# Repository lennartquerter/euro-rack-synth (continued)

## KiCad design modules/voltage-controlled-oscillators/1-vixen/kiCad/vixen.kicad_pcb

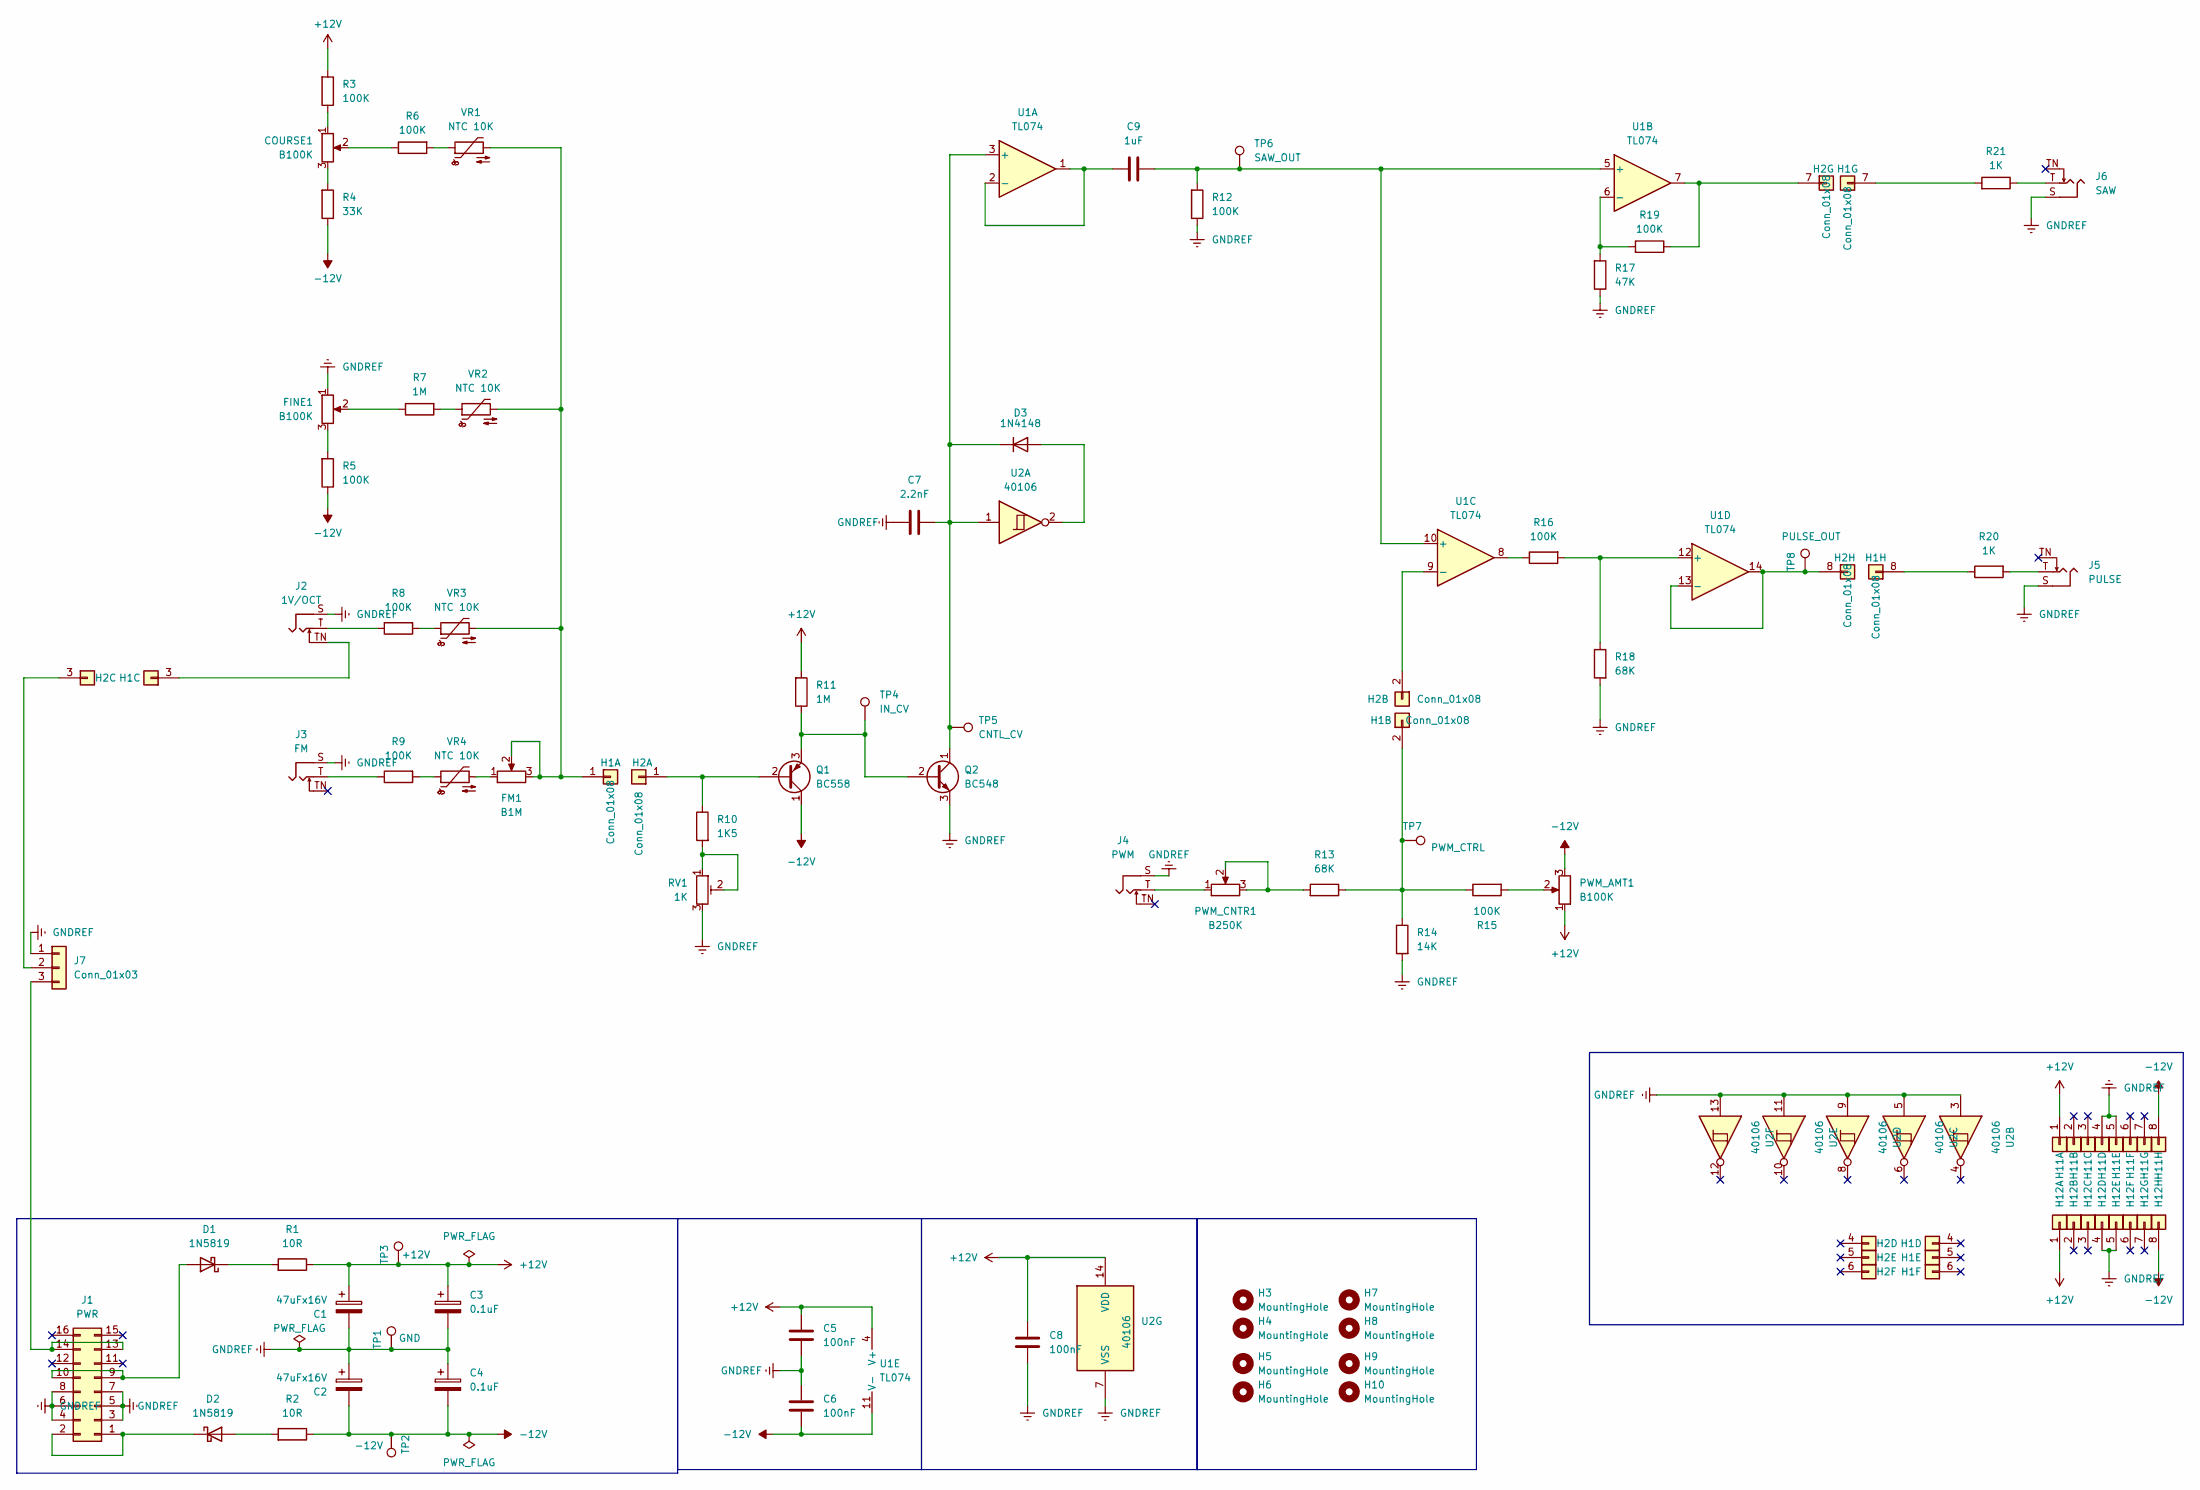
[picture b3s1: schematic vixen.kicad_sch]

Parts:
C1, C2: 47uFx16V; CP_Radial_D5.0mm_P2.00mm
C3, C4: 0.1uF; CP_Radial_D4.0mm_P2.00mm
C5, C6, C8: 100nF; C_RECT_WIMA_0.1uF
C7: 2.2nF; C_RECT_WIMA_0.1uF
C9: 1uF; C_RECT_MKT_1uF
COURSE1: B100K; Potentiometer_TT_P0915N
D1, D2: 1N5819; D_DO-41_SOD81_P10.16mm_Horizontal
D3: 1N4148; D_DO-35_SOD27_P7.62mm_Horizontal
FINE1: B100K; Potentiometer_TT_P0915N
FM1: B1M; Potentiometer_TT_P0915N
H1, H12: Conn_01x08; PinHeader_1x08_P2.54mm_Vertical
H2, H11: Conn_01x08; PinSocket_1x08_P2.54mm_Vertical
H3, H4, H5, H6, H7, H8, H9, H10: MountingHole; MountingHole_3.5mm
J1: PWR; IDC-Header_2x08_P2.54mm_Vertical
J2: 1V/OCT; Jack_3.5mm_QingPu_WQP-PJ398SM_Vertical_CircularHoles
J3: FM; Jack_3.5mm_QingPu_WQP-PJ398SM_Vertical_CircularHoles
J4: PWM; Jack_3.5mm_QingPu_WQP-PJ398SM_Vertical_CircularHoles
J5: PULSE; Jack_3.5mm_QingPu_WQP-PJ398SM_Vertical_CircularHoles
J6: SAW; Jack_3.5mm_QingPu_WQP-PJ398SM_Vertical_CircularHoles
J7: Conn_01x03; PinHeader_1x03_P2.54mm_Vertical
PWM_AMT1: B100K; Potentiometer_TT_P0915N
PWM_CNTR1: B250K; Potentiometer_Alpha_RD901F-40-00D_Single_Vertical_CircularH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
Q1: BC558; TO-92_HandSolder
Q2: BC548; TO-92_HandSolder
R1, R2: 10R; R_Default (DIN0207)
R3, R5, R6, R8, R9, R12, R15, R16, R19: 100K; R_Default (DIN0207)
R4: 33K; R_Default (DIN0207)
R7, R11: 1M; R_Default (DIN0207)
R10: 1K5; R_Default (DIN0207)
R13, R18: 68K; R_Default (DIN0207)
R14: 14K; R_Default (DIN0207)
R17: 47K; R_Default (DIN0207)
R20, R21: 1K; R_Default (DIN0207)
RV1: 1K; Potentiometer_Bourns_3296W_Vertical
TP1: GND; Pin_D1.0mm_L10.0mm
TP2: -12V; Pin_D1.0mm_L10.0mm
TP3: +12V; Pin_D1.0mm_L10.0mm
TP4: IN_CV; Pin_D1.0mm_L10.0mm
TP5: CNTL_CV; Pin_D1.0mm_L10.0mm
TP6: SAW_OUT; Pin_D1.0mm_L10.0mm
TP7: PWM_CTRL; Pin_D1.0mm_L10.0mm
TP8: PULSE_OUT; Pin_D1.0mm_L10.0mm
U1: TL074; DIP-14_W7.62mm_Socket_LongPads
U2: 40106; DIP-14_W7.62mm_Socket_LongPads
VR1, VR2, VR3, VR4: NTC 10K; R_Axial_DIN0207_L6.3mm_D2.5mm_P5.08mm_Vertical

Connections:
+12V: C1.1, C3.1, C5.1, C8.1, H11.1 (Pin_3), H12.1, PWM_AMT1.1, R1.2, R3.1, R11.1, TP3.1, U1.4 (V+), U2.14 (VDD)
-12V: C2.2, C4.2, C6.2, H11.8, H12.8, PWM_AMT1.3, Q1.1 (C), R2.2, R4.2, R5.2, TP2.1, U1.11 (V-)
GNDREF: C1.2, C2.1, C3.2, C4.1, C5.2, C6.1, C7.2, C8.2, FINE1.1, H11.4, H11.5, H12.4, H12.5, J1.3 (GND), J1.4 (GND), J1.5 (GND), J1.6 (GND), J1.7 (GND), J1.8 (GND), J2.S, J3.S, J4.S, J5.S, J6.S, J7.1, Q2.3 (E), R12.2, R14.1, R17.2, R18.1, RV1.3, TP1.1, U2.3, U2.5, U2.7 (VSS), U2.9, U2.11, U2.13
unnamed: COURSE1.1, R3.2
unnamed: COURSE1.2, R6.2
unnamed: COURSE1.3, R4.1
unnamed: D1.2 (A), J1.9 (+12V), J1.10 (+12V)
unnamed: D1.1 (K), R1.1
unnamed: D2.2 (A), R2.1
unnamed: D2.1 (K), J1.1 (-12V), J1.2 (-12V)
unnamed: D3.2 (A), U2.2
unnamed: C7.1, D3.1 (K), Q2.1 (C), TP5.1, U1.3 (+), U2.1
unnamed: FINE1.2, R7.2
unnamed: FINE1.3, R5.1
unnamed: FM1.1, VR4.2
unnamed: FM1.2, FM1.3, H1.1, VR1.2, VR2.2, VR3.2
unnamed: H1.2, R13.2, R14.2, R15.2, TP7.1
unnamed: H1.3, J2.TN
unnamed: H1.7, R21.1
unnamed: H1.8, R20.2
unnamed: H2.1 (Pin_3), Q1.2 (B), R10.2
unnamed: H2.2, U1.9 (-)
unnamed: H2.3, J7.2
unnamed: H2.7, R19.2, U1.7
unnamed: H2.8, TP8.1, U1.13 (-), U1.14
unnamed: J2.T, R8.2
unnamed: J3.T, R9.2
unnamed: J4.T, PWM_CNTR1.1
unnamed: J5.T, R20.1
unnamed: J6.T, R21.2
unnamed: J1.13 (CV), J1.14 (CV), J7.3
unnamed: PWM_AMT1.2, R15.1
unnamed: PWM_CNTR1.2, PWM_CNTR1.3, R13.1
unnamed: Q1.3 (E), Q2.2 (B), R11.2, TP4.1
unnamed: R6.1, VR1.1
unnamed: R7.1, VR2.1
unnamed: R8.1, VR3.1
unnamed: R9.1, VR4.1
unnamed: R10.1, RV1.1, RV1.2
unnamed: R16.2, U1.8
unnamed: C9.1, U1.1, U1.2 (-)
unnamed: C9.2, R12.1, TP6.1, U1.5 (+), U1.10 (+)
unnamed: R17.1, R19.1, U1.6 (-)
unnamed: R16.1, R18.2, U1.12 (+)

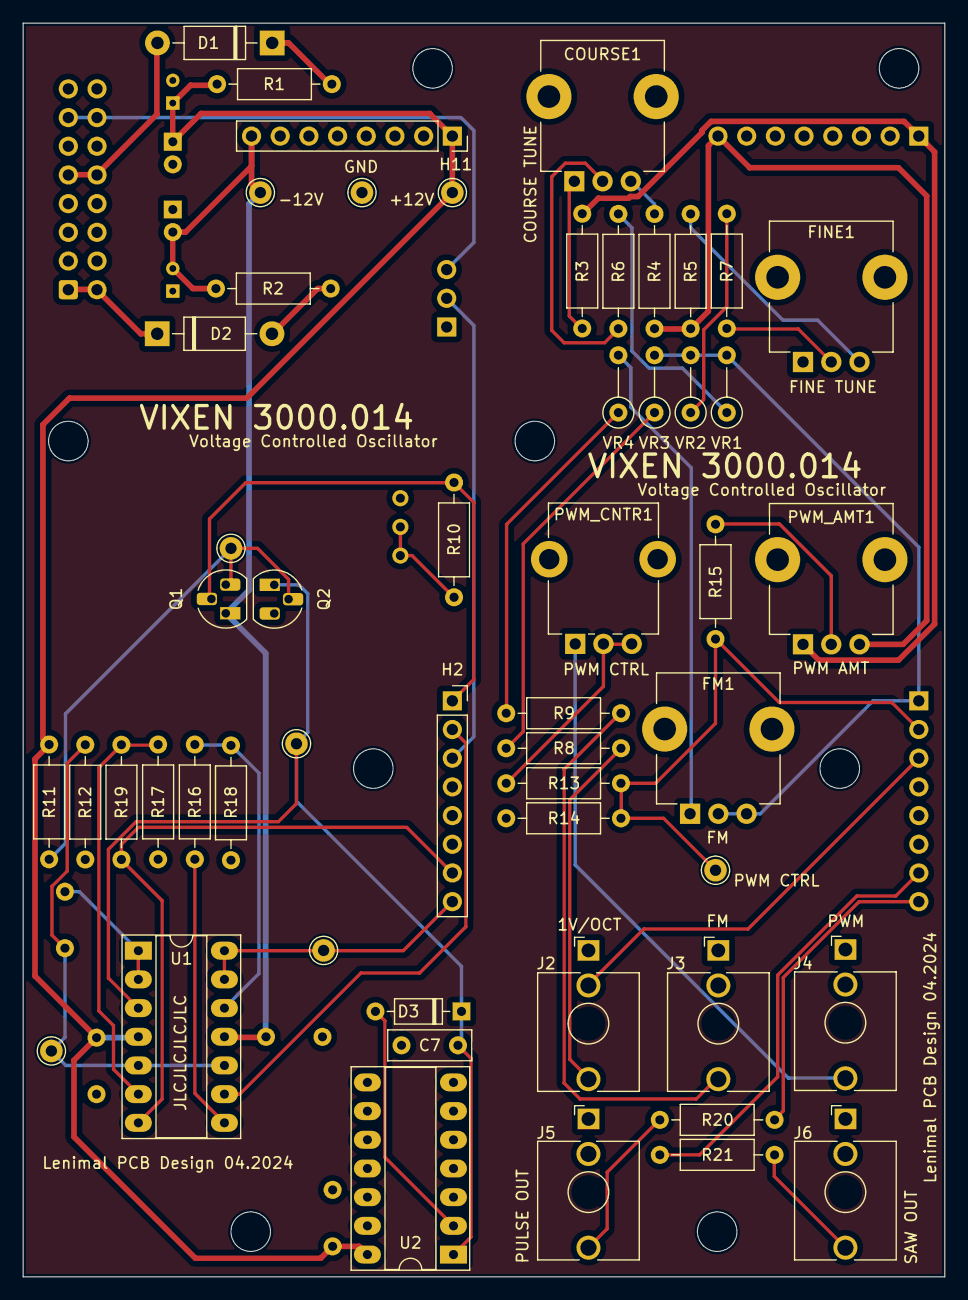
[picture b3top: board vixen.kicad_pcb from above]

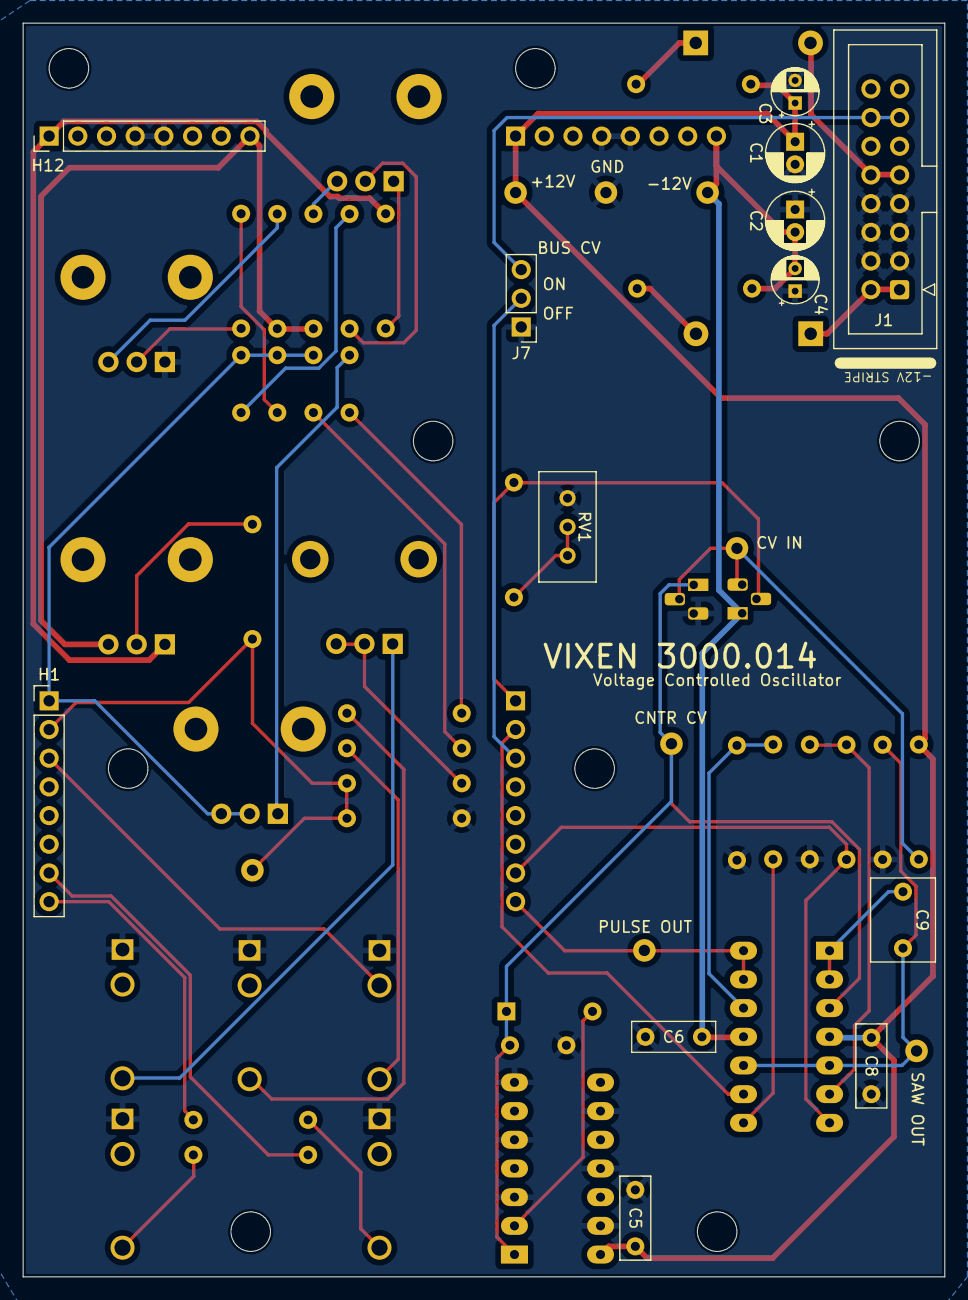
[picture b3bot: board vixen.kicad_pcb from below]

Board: 2 copper layers, 81.6 x 111.0 mm, 74 parts (13 on the bottom side), 44 nets.

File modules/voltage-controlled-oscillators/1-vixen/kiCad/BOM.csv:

"Reference","Value","Datasheet","Footprint","Qty","DNP"
"C1,C2","47uFx16V","~","Capacitor_THT:CP_Radial_D5.0mm_P2.00mm","2",""
"C3,C4,C5,C6,C8","0.1uF","~","Capacitor_THT:CP_Radial_D4.0mm_P2.00mm","5",""
"C7","2.2nF","~","Synth:C_RECT_WIMA_0.1uF","1",""
"C9","1 uF","~","Synth:C_RECT_MKT_1uF","1",""
"COURSE1,FINE1,PWM_AMT1","B100K","~","Synth:Potentiometer_TT_P0915N","3",""
"D1,D2","1N5819","http://www.vishay.com/docs/88525/1n5817.pdf","Synth:D_DO-41_SOD81_P10.16mm_Horizontal","2",""
"D3","1N4148","https://assets.nexperia.com/documents/data-sheet/1N4148_1N4448.pdf","Synth:D_DO-35_SOD27_P7.62mm_Horizontal","1",""
"FM1","B1M","~","Synth:Potentiometer_TT_P0915N","1",""
"H1","TOP_SGN","~","Synth:PinHeader_1x08_P2.54mm_Vertical","1",""
"H2","BTN_SGN","~","Synth:PinSocket_1x08_P2.54mm_Vertical","1",""
"H3,H4,H5,H6,H7,H8,H9,H10","MountingHole","~","MountingHole:MountingHole_3.5mm","8",""
"H11","BTM_PWR","~","Synth:PinSocket_1x08_P2.54mm_Vertical","1",""
"H12","TOP_PWR","~","Synth:PinHeader_1x08_P2.54mm_Vertical","1",""
"J1","PWR","~","Synth:IDC-Header_2x08_P2.54mm_Vertical","1",""
"J2","1V/OCT","~","Synth:Jack_3.5mm_QingPu_WQP-PJ398SM_Vertical_CircularHoles","1",""
"J3","FM","~","Synth:Jack_3.5mm_QingPu_WQP-PJ398SM_Vertical_CircularHoles","1",""
"J4","PWM","~","Synth:Jack_3.5mm_QingPu_WQP-PJ398SM_Vertical_CircularHoles","1",""
"J5","PULSE","~","Synth:Jack_3.5mm_QingPu_WQP-PJ398SM_Vertical_CircularHoles","1",""
"J6","SAW","~","Synth:Jack_3.5mm_QingPu_WQP-PJ398SM_Vertical_CircularHoles","1",""
"J7","Conn_01x03","~","Connector_PinHeader_2.54mm:PinHeader_1x03_P2.54mm_Vertical","1",""
"PWM_CNTR1","B250K","~","Synth:Potentiometer_Alpha_RD901F-40-00D_Single_Vertical_CircularHoles","1",""
"Q1","BC558","https://www.onsemi.com/pub/Collateral/BC556BTA-D.pdf","Package_TO_SOT_THT:TO-92_Inline","1",""
"Q2","BC548","https://www.onsemi.com/pub/Collateral/BC550-D.pdf","Package_TO_SOT_THT:TO-92_Inline","1",""
"R1,R2","10","~","Synth:R_Default (DIN0207)","2",""
"R3,R5,R6,R8,R9,R12,R15,R16,R19","100K","~","Synth:R_Default (DIN0207)","9",""
"R4","33K","~","Synth:R_Default (DIN0207)","1",""
"R7,R11","1M","~","Synth:R_Default (DIN0207)","2",""
"R10","1.5K","~","Synth:R_Default (DIN0207)","1",""
"R13,R18","68K","~","Synth:R_Default (DIN0207)","2",""
"R14","14K","~","Synth:R_Default (DIN0207)","1",""
"R17","47K","~","Synth:R_Default (DIN0207)","1",""
"R20,R21,RV1","1K","~","-- mixed values --","3",""
"TP1","GND","~","Connector_Pin:Pin_D1.0mm_L10.0mm","1",""
"TP2","-12V","~","Connector_Pin:Pin_D1.0mm_L10.0mm","1",""
"TP3","+12V","~","Connector_Pin:Pin_D1.0mm_L10.0mm","1",""
"TP4","IN_CV","~","Connector_Pin:Pin_D1.0mm_L10.0mm","1",""
"TP5","CNTL_CV","~","Connector_Pin:Pin_D1.0mm_L10.0mm","1",""
"TP6","SAW_OUT","~","Connector_Pin:Pin_D1.0mm_L10.0mm","1",""
"TP7","PWM_CTRL","~","Connector_Pin:Pin_D1.0mm_L10.0mm","1",""
"TP8","PULSE_OUT","~","Connector_Pin:Pin_D1.0mm_L10.0mm","1",""
"U1","TL074","http://www.ti.com/lit/ds/symlink/tl071.pdf","Package_DIP:DIP-14_W7.62mm_Socket_LongPads","1",""
"U2","40106","https://assets.nexperia.com/documents/data-sheet/HEF40106B.pdf","Package_DIP:DIP-14_W7.62mm_Socket_LongPads","1",""
"VR1,VR2,VR3,VR4","NTC 10K","~","Resistor_THT:R_Axial_DIN0207_L6.3mm_D2.5mm_P5.08mm_Vertical","4",""

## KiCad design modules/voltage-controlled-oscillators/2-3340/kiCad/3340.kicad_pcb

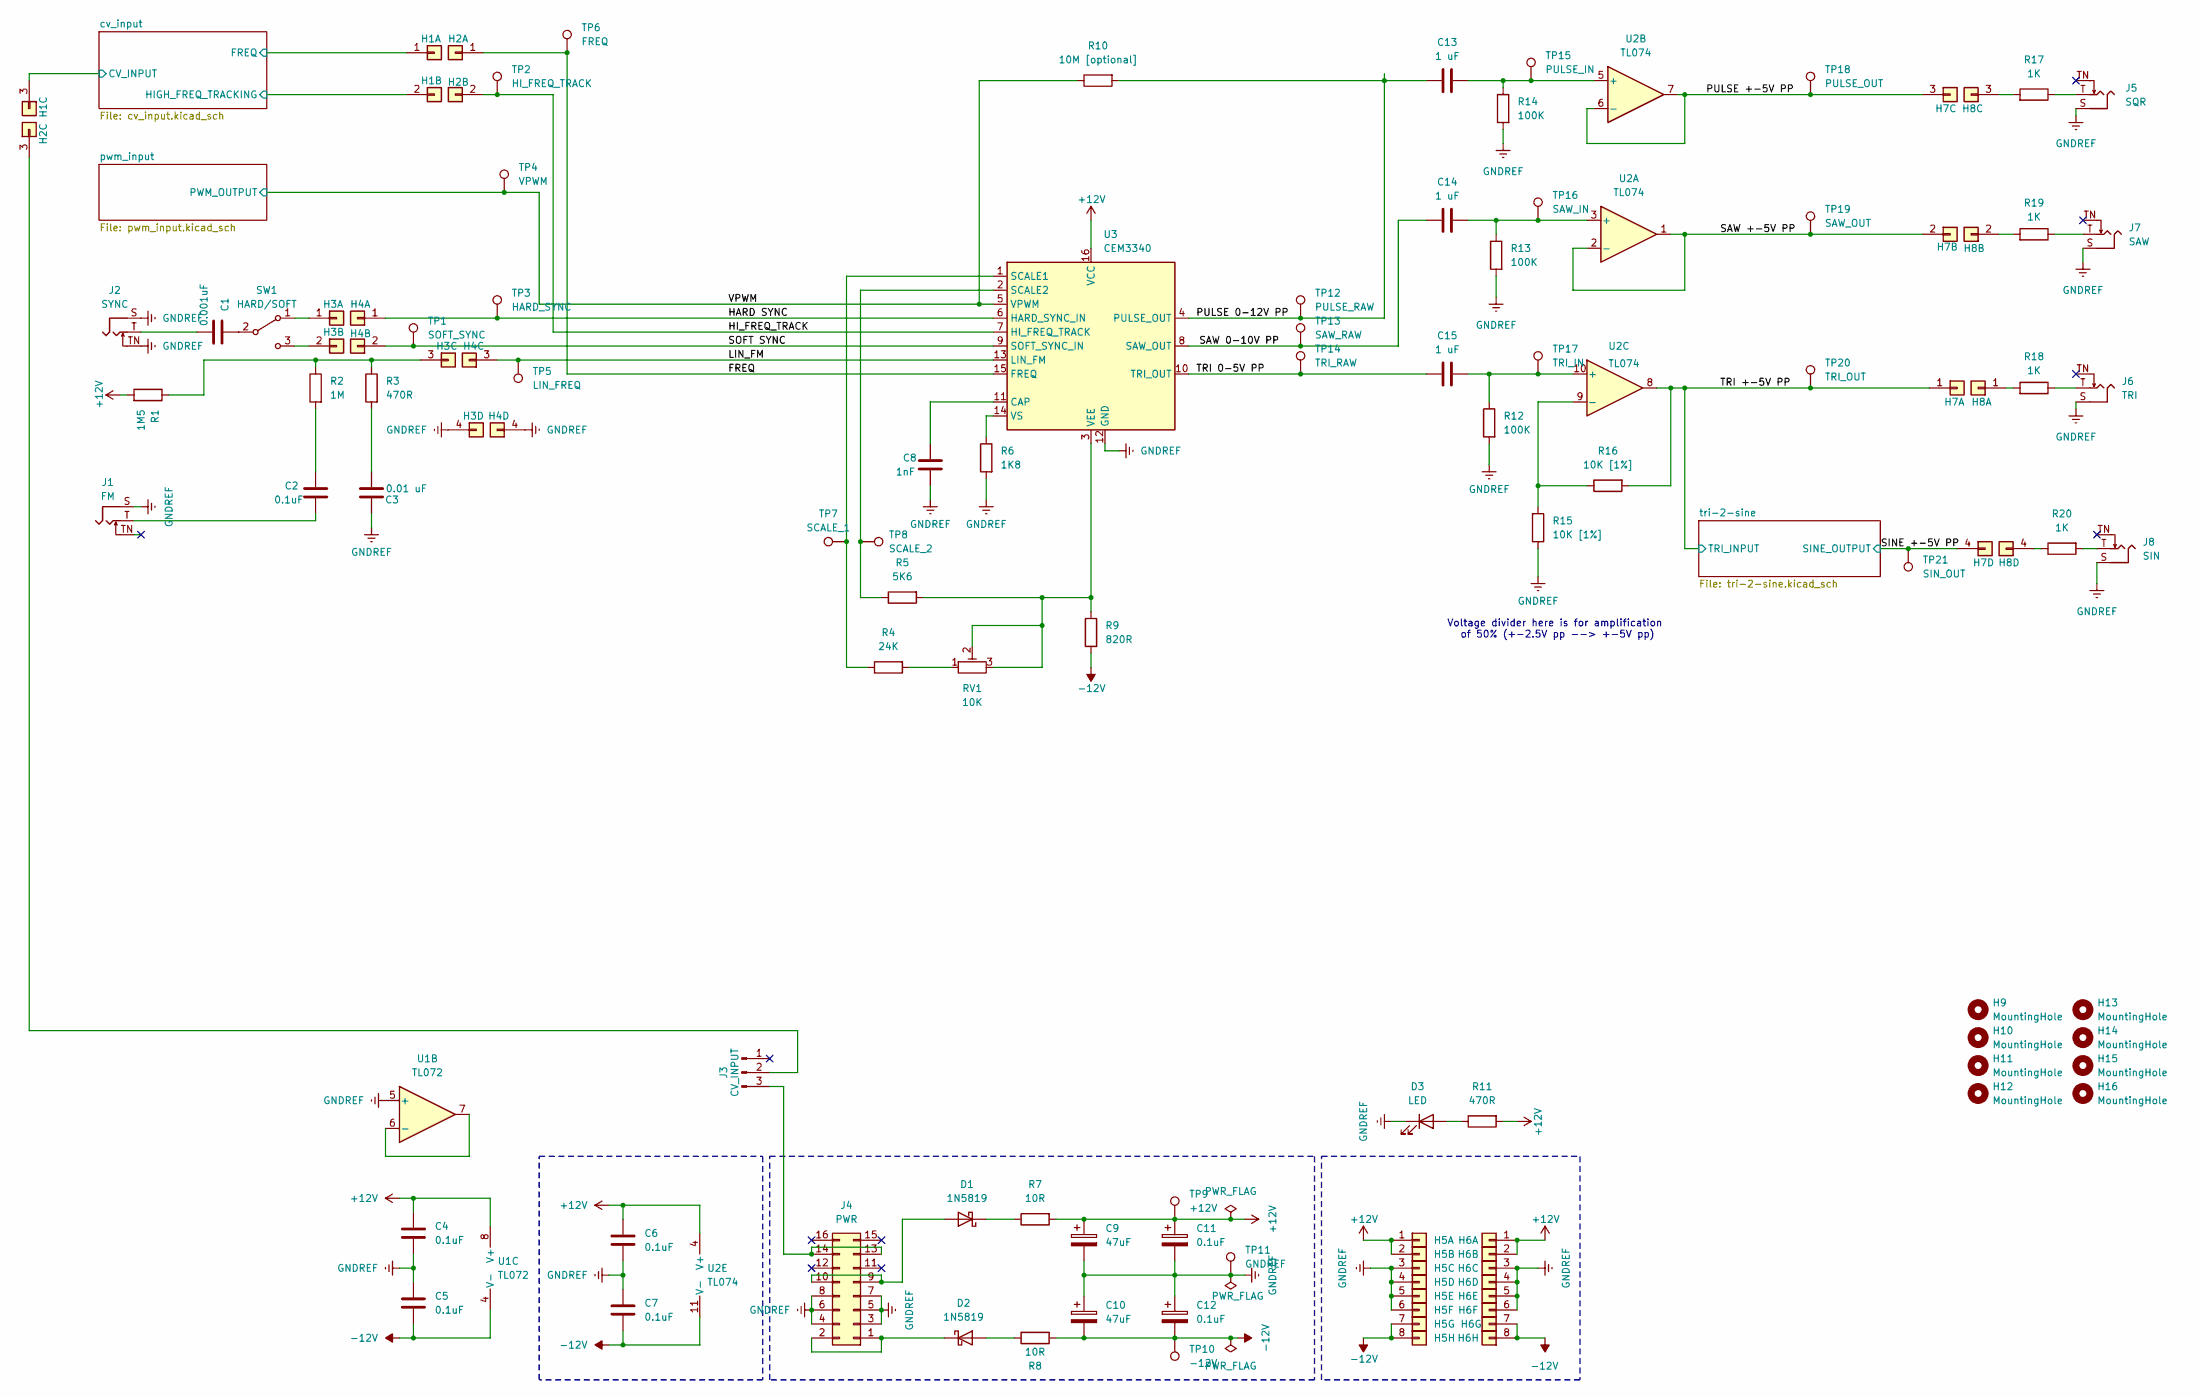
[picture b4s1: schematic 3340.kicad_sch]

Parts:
C1: 0.001uF; C_RECT_WIMA_0.1uF
C2, C4, C5, C6, C7: 0.1uF; C_RECT_WIMA_0.1uF
C3: 0.01 uF; C_RECT_WIMA_0.1uF
C8: 1nF; C_RECT_WIMA_0.1uF
C9, C10: 47uF; CP_Radial_D6.3mm_P2.50mm
C11, C12: 0.1uF; CP_Radial_D4.0mm_P2.00mm
C13, C14, C15: 1 uF; C_RECT_MKT_1uF
D1, D2: 1N5819; D_DO-41_SOD81_P10.16mm_Horizontal
D3: LED; LED_D5.0mm (center Aligned)
H1, H3, H8: PinHeader_1x04_P2.54mm_Vertical
H2, H4, H7: PinSocket_1x04_P2.54mm_Vertical
H5: PinHeader_1x08_P2.54mm_Vertical
H6: PinSocket_1x08_P2.54mm_Vertical
H9, H10, H11, H12, H13, H14, H15, H16: MountingHole; MountingHole_3.2mm_M3
J1: FM; Jack_3.5mm_QingPu_WQP-PJ398SM_Vertical_CircularHoles
J2: SYNC; Jack_3.5mm_QingPu_WQP-PJ398SM_Vertical_CircularHoles
J3: CV_INPUT; PinHeader_1x03_P2.54mm_Vertical
J4: PWR; IDC-Header_2x08_P2.54mm_Vertical
J5: SQR; Jack_3.5mm_QingPu_WQP-PJ398SM_Vertical_CircularHoles
J6: TRI; Jack_3.5mm_QingPu_WQP-PJ398SM_Vertical_CircularHoles
J7: SAW; Jack_3.5mm_QingPu_WQP-PJ398SM_Vertical_CircularHoles
J8: SIN; Jack_3.5mm_QingPu_WQP-PJ398SM_Vertical_CircularHoles
R1: 1M5; R_Default (DIN0207)
R2: 1M; R_Default (DIN0207)
R3, R11: 470R; R_Default (DIN0207)
R4: 24K; R_Default (DIN0207)
R5: 5K6; R_Default (DIN0207)
R6: 1K8; R_Default (DIN0207)
R7, R8: 10R; R_Default (DIN0207)
R9: 820R; R_Default (DIN0207)
R10: 10M [optional]; R_Default (DIN0207)
R12, R13, R14: 100K; R_Default (DIN0207)
R15, R16: 10K [1%]; R_Default (DIN0207)
R17, R18, R19, R20: 1K; R_Default (DIN0207)
RV1: 10K; Potentiometer_Bourns_3296W_Vertical
SW1: HARD/SOFT; SW_default
TP1: SOFT_SYNC; Pin_D1.0mm_L10.0mm
TP2: HI_FREQ_TRACK; Pin_D1.0mm_L10.0mm
TP3: HARD_SYNC; Pin_D1.0mm_L10.0mm
TP4: VPWM; Pin_D1.0mm_L10.0mm
TP5: LIN_FREQ; Pin_D1.0mm_L10.0mm
TP6: FREQ; Pin_D1.0mm_L10.0mm
TP7: SCALE_1; Pin_D1.0mm_L10.0mm
TP8: SCALE_2; Pin_D1.0mm_L10.0mm
TP9: +12V; Pin_D1.0mm_L10.0mm
TP10: -12V; Pin_D1.0mm_L10.0mm
TP11: GNDREF; Pin_D1.0mm_L10.0mm
TP12: PULSE_RAW; Pin_D1.0mm_L10.0mm
TP13: SAW_RAW; Pin_D1.0mm_L10.0mm
TP14: TRI_RAW; Pin_D1.0mm_L10.0mm
TP15: PULSE_IN; Pin_D1.0mm_L10.0mm
TP16: SAW_IN; Pin_D1.0mm_L10.0mm
TP17: TRI_IN; Pin_D1.0mm_L10.0mm
TP18: PULSE_OUT; Pin_D1.0mm_L10.0mm
TP19: SAW_OUT; Pin_D1.0mm_L10.0mm
TP20: TRI_OUT; Pin_D1.0mm_L10.0mm
TP21: SIN_OUT; Pin_D1.0mm_L10.0mm
U1: TL072; DIP-8_W7.62mm_Socket_LongPads
U2: TL074; DIP-14_W7.62mm_Socket_LongPads
U3: CEM3340; DIP-16_W7.62mm_Socket_LongPads

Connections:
+12V: C4.1, C6.1, C9.1, C11.1, H5.1, H5.2, H6.1 (Pin_3), H6.2, R1.1, R7.1, R11.1, TP9.1, U1.8 (V+), U2.4 (V+), U3.16 (VCC); also elsewhere on the board
-12V: C5.2, C7.2, C10.2, C12.2, H5.7, H5.8, H6.7, H6.8, R8.1, R9.1, TP10.1, U1.4 (V-), U2.11 (V-); also elsewhere on the board
/FREQ: H2.1, TP6.1, U3.15 (FREQ)
/HARD SYNC: H4.1, TP3.1, U3.6 (HARD_SYNC_IN)
/HI_FREQ_TRACK: H2.2, TP2.1, U3.7 (HI_FREQ_TRACK)
/LIN_FM: H4.3, TP5.1, U3.13 (LIN_FM)
/PULSE 0-12V PP: C13.1, R10.1, TP12.1, U3.4 (PULSE_OUT)
/PULSE +-5V PP: H7.3, TP18.1, U2.6 (-), U2.7
/SAW 0-10V PP: C14.1, TP13.1, U3.8 (SAW_OUT)
/SAW +-5V PP: H7.2, TP19.1, U2.1, U2.2 (-)
/SINE +-5V PP: H7.4, TP21.1; also elsewhere on the board
/SOFT SYNC: H4.2, TP1.1, U3.9 (SOFT_SYNC_IN)
/TRI 0-5V PP: C15.1, TP14.1, U3.10 (TRI_OUT)
/TRI +-5V PP: H7.1, R16.1, TP20.1, U2.8; also elsewhere on the board
/VPWM: R10.2, TP4.1, U3.5 (VPWM); also elsewhere on the board
/cv_input/CV_INPUT: H1.3; also elsewhere on the board
/cv_input/FREQ: H1.1; also elsewhere on the board
/cv_input/HIGH_FREQ_TRACKING: H1.2; also elsewhere on the board
GNDREF: C3.2, C4.2, C5.1, C6.2, C7.1, C8.1, C9.2, C10.1, C11.2, C12.1, D3.1 (K), H3.4, H4.4, H5.3, H5.4, H5.5, H5.6, H6.3, H6.4, H6.5, H6.6, J1.S, J2.S, J2.TN, J4.3 (GND), J4.4 (GND), J4.5 (GND), J4.6 (GND), J4.7 (GND), J4.8 (GND), J5.S, J6.S, J7.S, J8.S, R6.1, R12.1, R13.1, R14.1, R15.2, TP11.1, U1.5 (+), U3.12 (GND); also elsewhere on the board
unnamed: C1.1, J2.T
unnamed: C2.1, J1.T
unnamed: C2.2, R2.1
unnamed: C3.1, R3.1
unnamed: D1.2 (A), J4.9 (+12V), J4.10 (+12V)
unnamed: D1.1 (K), R7.2
unnamed: D2.2 (A), R8.2
unnamed: D2.1 (K), J4.1 (-12V), J4.2 (-12V)
unnamed: D3.2 (A), R11.2
unnamed: H2.3, J3.2
unnamed: H3.1, SW1.1 (A)
unnamed: H3.2, SW1.3 (C)
unnamed: H3.3, R1.2, R2.2, R3.2
unnamed: H8.1, R18.1
unnamed: H8.2, R19.1
unnamed: H8.3, R17.1
unnamed: H8.4, R20.2
unnamed: J3.3, J4.13 (CV), J4.14 (CV)
unnamed: J5.T, R17.2
unnamed: J6.T, R18.2
unnamed: J7.T, R19.2
unnamed: J8.T, R20.1
unnamed: R4.1, RV1.1
unnamed: C1.2, SW1.2 (B)
unnamed: U1.6 (-), U1.7
unnamed: C14.2, R13.2, TP16.1, U2.3 (+)
unnamed: C13.2, R14.2, TP15.1, U2.5 (+)
unnamed: C15.2, R12.2, TP17.1, U2.10 (+)
unnamed: R15.1, R16.2, U2.9 (-)
unnamed: C8.2, U3.11 (CAP)
unnamed: R4.2, TP7.1, U3.1 (SCALE1)
unnamed: R5.2, TP8.1, U3.2 (SCALE2)
unnamed: R5.1, R9.2, RV1.2, RV1.3, U3.3 (VEE)
unnamed: R6.2, U3.14 (VS)

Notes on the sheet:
Voltage divider here is for amplification of 50% (+-2.5V pp --> +-5V pp)

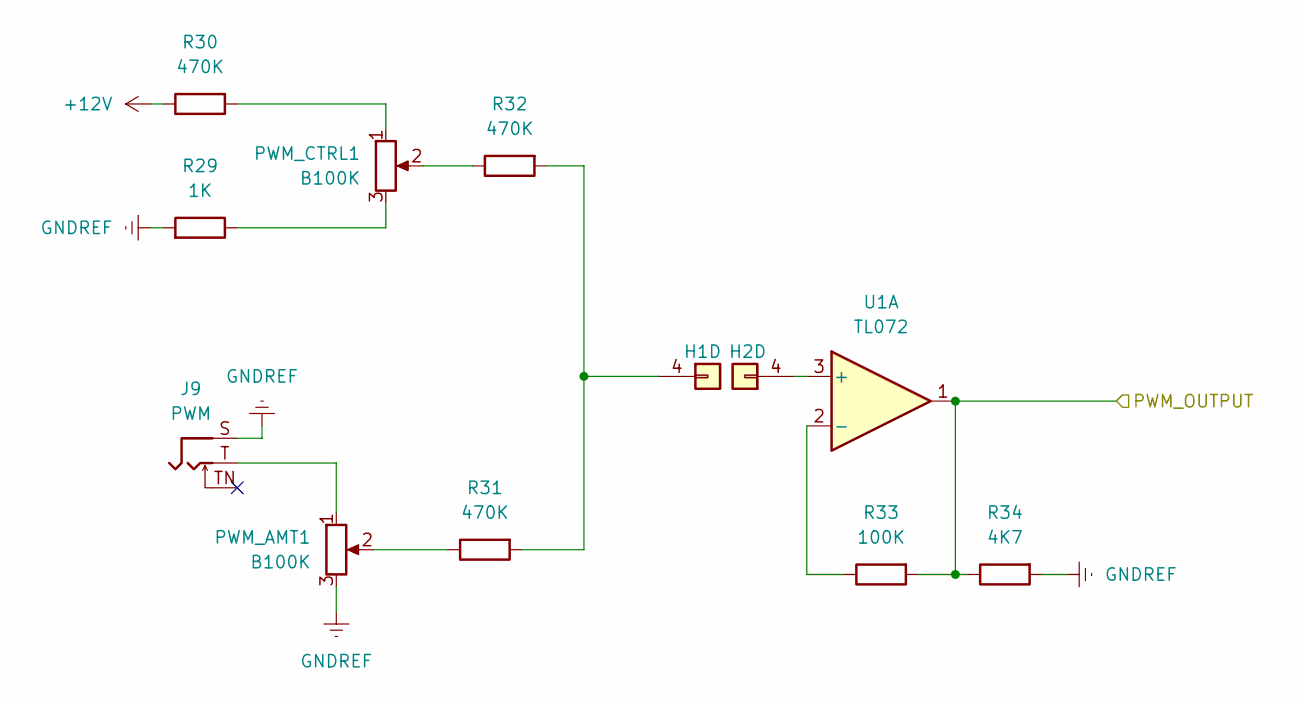
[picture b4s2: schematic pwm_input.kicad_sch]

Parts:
H1: PinHeader_1x04_P2.54mm_Vertical
H2: PinSocket_1x04_P2.54mm_Vertical
J9: PWM; Jack_3.5mm_QingPu_WQP-PJ398SM_Vertical_CircularHoles
PWM_AMT1: B100K; Potentiometer_Alpha_RD901F-40-00D_Single_Vertical_CircularH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
PWM_CTRL1: B100K; Potentiometer_Alpha_RD901F-40-00D_Single_Vertical_CircularH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
R29: 1K; R_Default (DIN0207)
R30, R31, R32: 470K; R_Default (DIN0207)
R33: 100K; R_Default (DIN0207)
R34: 4K7; R_Default (DIN0207)
U1: TL072; DIP-8_W7.62mm_Socket_LongPads

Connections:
+12V: R30.2; also elsewhere on the board
/VPWM: R33.1, R34.2, U1.1; also elsewhere on the board
GNDREF: J9.S, PWM_AMT1.3, R29.1, R34.1; also elsewhere on the board
unnamed: H1.4, R31.1, R32.1
unnamed: H2.4, U1.3 (+)
unnamed: J9.T, PWM_AMT1.1
unnamed: PWM_AMT1.2, R31.2
unnamed: PWM_CTRL1.1, R30.1
unnamed: PWM_CTRL1.2, R32.2
unnamed: PWM_CTRL1.3, R29.2
unnamed: R33.2, U1.2 (-)

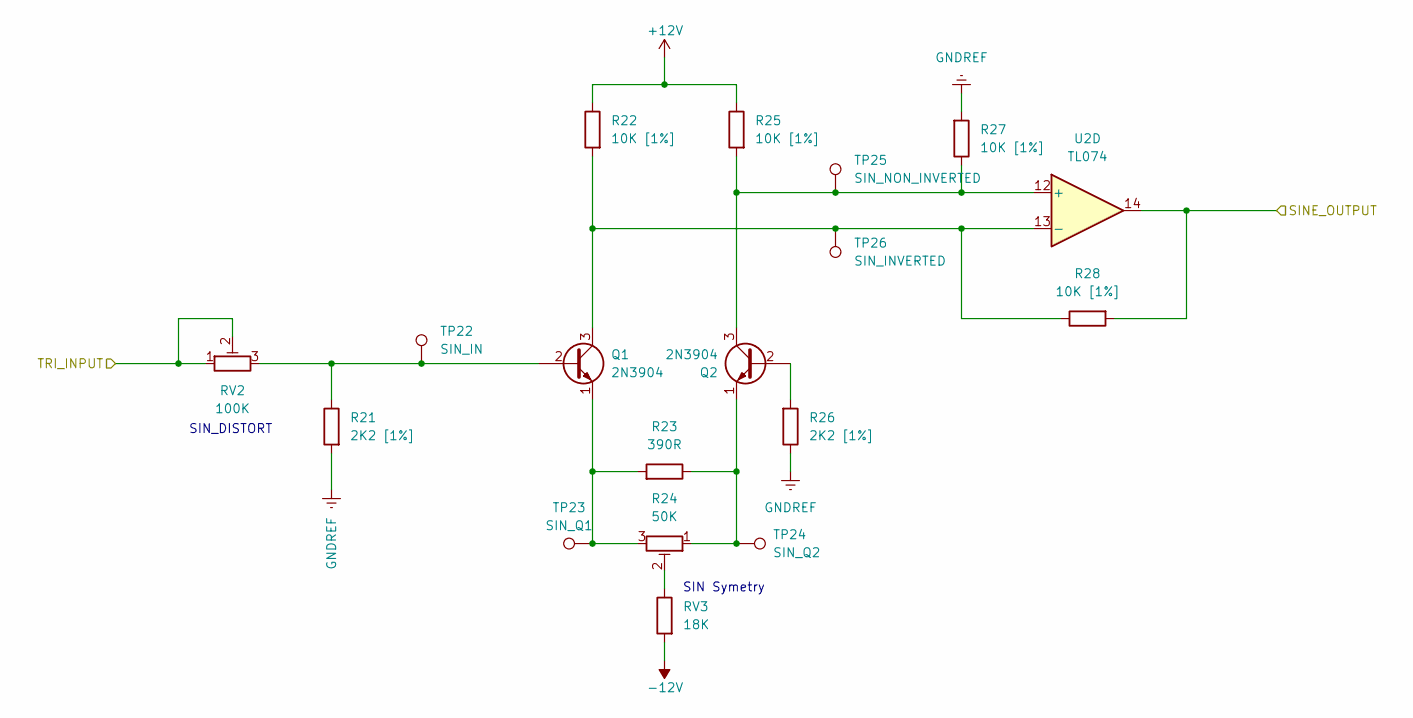
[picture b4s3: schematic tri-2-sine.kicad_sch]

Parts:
Q1, Q2: 2N3904; TO-92L_HandSolder
R21, R26: 2K2 [1%]; R_Default (DIN0207)
R22, R25, R27, R28: 10K [1%]; R_Default (DIN0207)
R23: 390R; R_Default (DIN0207)
R24: 50K; Potentiometer_Bourns_3296W_Vertical
RV2: 100K; Potentiometer_Bourns_3296W_Vertical
RV3: 18K; R_Default (DIN0207)
TP22: SIN_IN; Pin_D1.0mm_L10.0mm
TP23: SIN_Q1; Pin_D1.0mm_L10.0mm
TP24: SIN_Q2; Pin_D1.0mm_L10.0mm
TP25: SIN_NON_INVERTED; Pin_D1.0mm_L10.0mm
TP26: SIN_INVERTED; Pin_D1.0mm_L10.0mm
U2: TL074; DIP-14_W7.62mm_Socket_LongPads

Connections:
+12V: R22.2, R25.2; also elsewhere on the board
-12V: RV3.1; also elsewhere on the board
/SINE +-5V PP: R28.1, U2.14; also elsewhere on the board
/TRI +-5V PP: RV2.1, RV2.2; also elsewhere on the board
GNDREF: R21.1, R26.2, R27.1; also elsewhere on the board
unnamed: Q1.2 (B), R21.2, RV2.3, TP22.1
unnamed: Q1.3 (C), R22.1, R28.2, TP26.1, U2.13 (-)
unnamed: Q1.1 (E), R23.1, R24.3, TP23.1
unnamed: Q2.2 (B), R26.1
unnamed: Q2.3 (C), R25.1, R27.2, TP25.1, U2.12 (+)
unnamed: Q2.1 (E), R23.2, R24.1, TP24.1
unnamed: R24.2, RV3.2

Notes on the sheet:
SIN Symetry
SIN_DISTORT

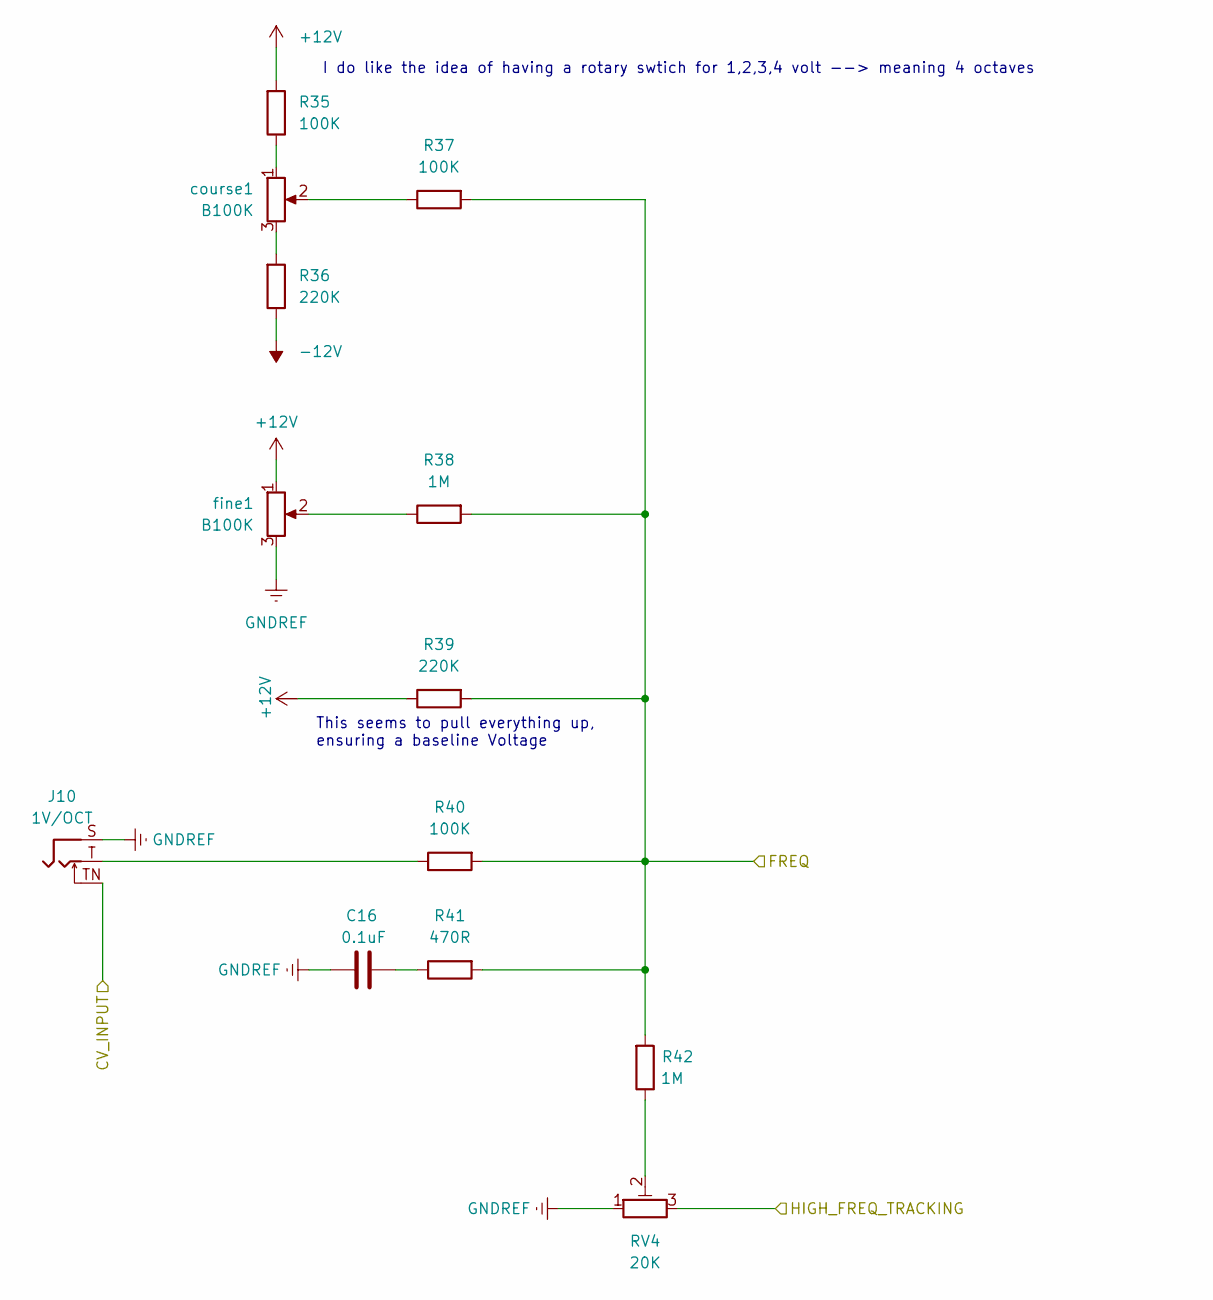
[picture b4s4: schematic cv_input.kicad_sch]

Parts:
C16: 0.1uF; C_RECT_WIMA_0.1uF
J10: 1V/OCT; Jack_3.5mm_QingPu_WQP-PJ398SM_Vertical_CircularHoles
R35, R37, R40: 100K; R_Default (DIN0207)
R36, R39: 220K; R_Default (DIN0207)
R38, R42: 1M; R_Default (DIN0207)
R41: 470R; R_Default (DIN0207)
RV4: 20K; Potentiometer_Bourns_3296W_Vertical
course1: B100K; Potentiometer_TT_P0915N
fine1: B100K; Potentiometer_TT_P0915N

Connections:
+12V: R35.1, R39.2, fine1.1; also elsewhere on the board
-12V: R36.2; also elsewhere on the board
/cv_input/CV_INPUT: J10.TN; also elsewhere on the board
/cv_input/FREQ: R37.1, R38.1, R39.1, R40.1, R41.1, R42.1; also elsewhere on the board
/cv_input/HIGH_FREQ_TRACKING: RV4.3; also elsewhere on the board
GNDREF: C16.2, J10.S, RV4.1, fine1.3; also elsewhere on the board
unnamed: C16.1, R41.2
unnamed: J10.T, R40.2
unnamed: R35.2, course1.1
unnamed: R36.1, course1.3
unnamed: R37.2, course1.2
unnamed: R38.2, fine1.2
unnamed: R42.2, RV4.2

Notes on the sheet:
I do like the idea of having a rotary swtich for 1,2,3,4 volt --> meaning 4 octaves
This seems to pull everything up, ensuring a baseline Voltage
